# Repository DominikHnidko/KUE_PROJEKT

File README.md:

# Elektroniczny stetoskop

## 📌 Opis projektu
Projekt przedstawia **elektroniczny stetoskop** przeznaczony do precyzyjnego odsłuchu i analizy dźwięków serca.  
Umożliwia on odsłuch w czasie rzeczywistym za pomocą słuchawek lub głośnika zewnętrznego.

Głównym celem systemu jest poprawa czytelności sygnału poprzez redukcję szumów i zakłóceń.

---

## ⚙️ Najważniejsze funkcje
- Odsłuch dźwięków serca w czasie rzeczywistym
- Wyjście audio przez słuchawki lub głośnik
- Wieloetapowa filtracja sygnału
- Redukcja:
  - zakłóceń sieciowych (50/60 Hz)
  - szumów otoczenia
  - częstotliwości spoza zakresu pracy serca
- Poprawa wykrywania szmerów sercowych

Układ działa i wzmacnia sygnał z pasma pracy serca.

---

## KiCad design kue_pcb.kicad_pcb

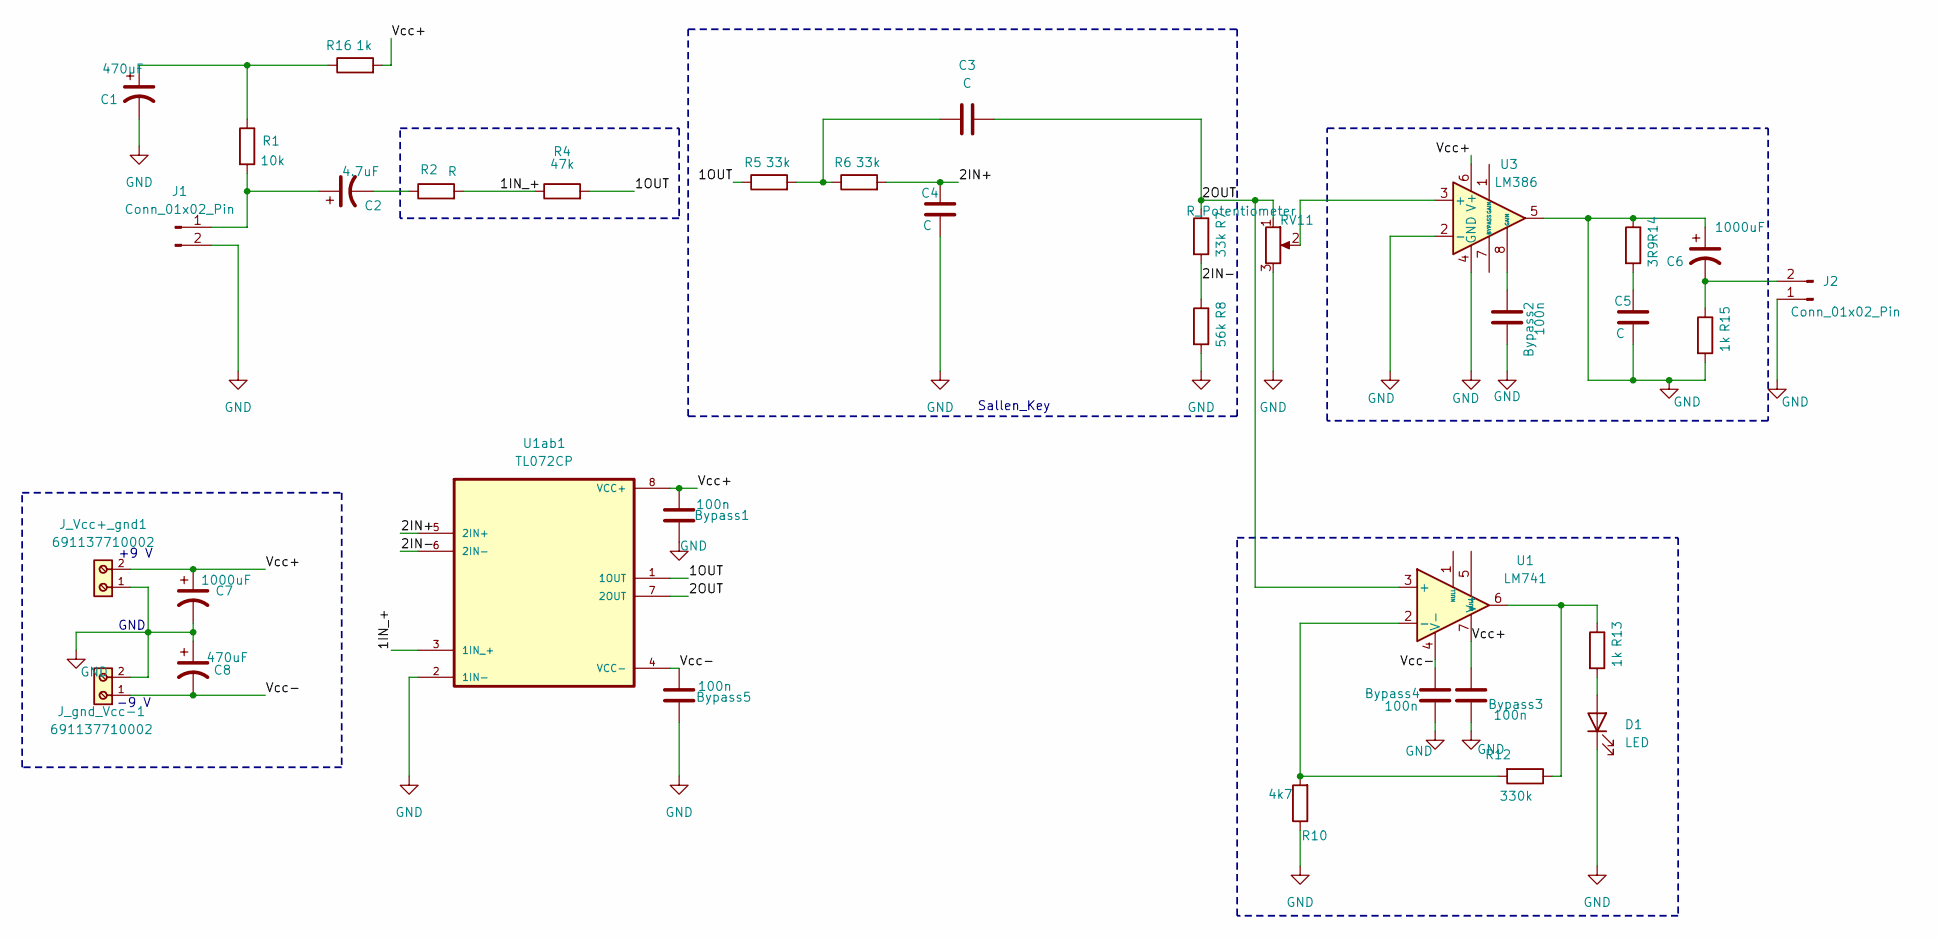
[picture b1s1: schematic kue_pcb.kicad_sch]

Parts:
Bypass1, Bypass2, Bypass3, Bypass4, Bypass5: 100n; XTAL_ZTA-2.44MG_100n_BP
C1, C8: 470uF; CAP_470uF_16V_kue
C2: 4.7uF; CAP_470uF_16V_kue
C3, C4: C; XTAL_ZTA-4.00MG_WIMA
C5: C; CAPRR254W54L508T318H736_ceramic
C6, C7: 1000uF; CP_Radial_D10.0mm_P5.00mm
D1: LED; LED_D5.0mm_Clear
J1, J2: Conn_01x02_Pin; Samtec_HPM-02-01-x-S_Straight_1x02_Pitch5.08mm
J_Vcc+_gnd1: 691137710002
J_gnd_Vcc-1: 691137710002
R1: 10k; STA_CF14_STP_kue10k_0.25w
R2: R; 2k2_kue_0.25W
R4: 47k; 47k_kue_0.25W
R5, R6: 33k; 1k_kue_0.25W
R7: 33k; 2k2_kue_0.25W
R8: 56k; 1k_kue_0.25W
R10: 4k7; 1k_kue_0.25W
R12: 330k; 1k_kue_0.25W
R13, R15, R16: 1k; 1k_kue_0.25W
R14: 3R9; 47k_kue_0.25W
RV11: R_Potentiometer; Potentiometer_Alps_RK163_Single_Horizontal
U1: LM741; DIP794W45P254L959H508Q8
U1ab1: TL072CP; DIP794W45P254L959H508Q8
U3: LM386; DIP794W45P254L959H508Q8_LM386

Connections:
/1IN_+: R2.2, R4.1, U1ab1.3 (1IN_+)
/1OUT: R4.2, R5.1, U1ab1.1 (1OUT)
/2IN+: C4.1, R6.2, U1ab1.5 (2IN+)
/2IN-: R7.2, R8.1, U1ab1.6 (2IN-)
/2OUT: C3.2, R7.1, RV11.1, U1.3 (+), U1ab1.7 (2OUT)
/Vcc+: Bypass1.1, Bypass3.1, C7.1, J_Vcc+_gnd1.2, R16.2, U1.7 (V+), U1ab1.8 (VCC+), U3.6 (V+)
/Vcc-: Bypass4.2, Bypass5.1, C8.2, J_gnd_Vcc-1.1, U1.4 (V-), U1ab1.4 (VCC-)
GND: Bypass1.2, Bypass2.1, Bypass3.2, Bypass4.1, Bypass5.2, C1.2, C4.2, C5.2, C6.1, C7.2, C8.1, D1.1 (K), J1.2, J2.1, J_Vcc+_gnd1.1, J_gnd_Vcc-1.2, R8.2, R10.1, R14.1, R15.2, RV11.3, U1ab1.2 (1IN-), U3.2 (-), U3.4 (GND), U3.5
unnamed: Bypass2.2, U3.8 (GAIN)
unnamed: C1.1, R1.1, R16.1
unnamed: C2.2, R2.1
unnamed: C3.1, R5.2, R6.1
unnamed: C5.1, R14.2
unnamed: D1.2 (A), R13.2
unnamed: C2.1, J1.1, R1.2
unnamed: C6.2, J2.2, R15.1
unnamed: R12.1, R13.1, U1.6
unnamed: R10.2, R12.2, U1.2 (-)
unnamed: RV11.2, U3.3 (+)

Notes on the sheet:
+9 V
GND
Sallen_Key
-9 V

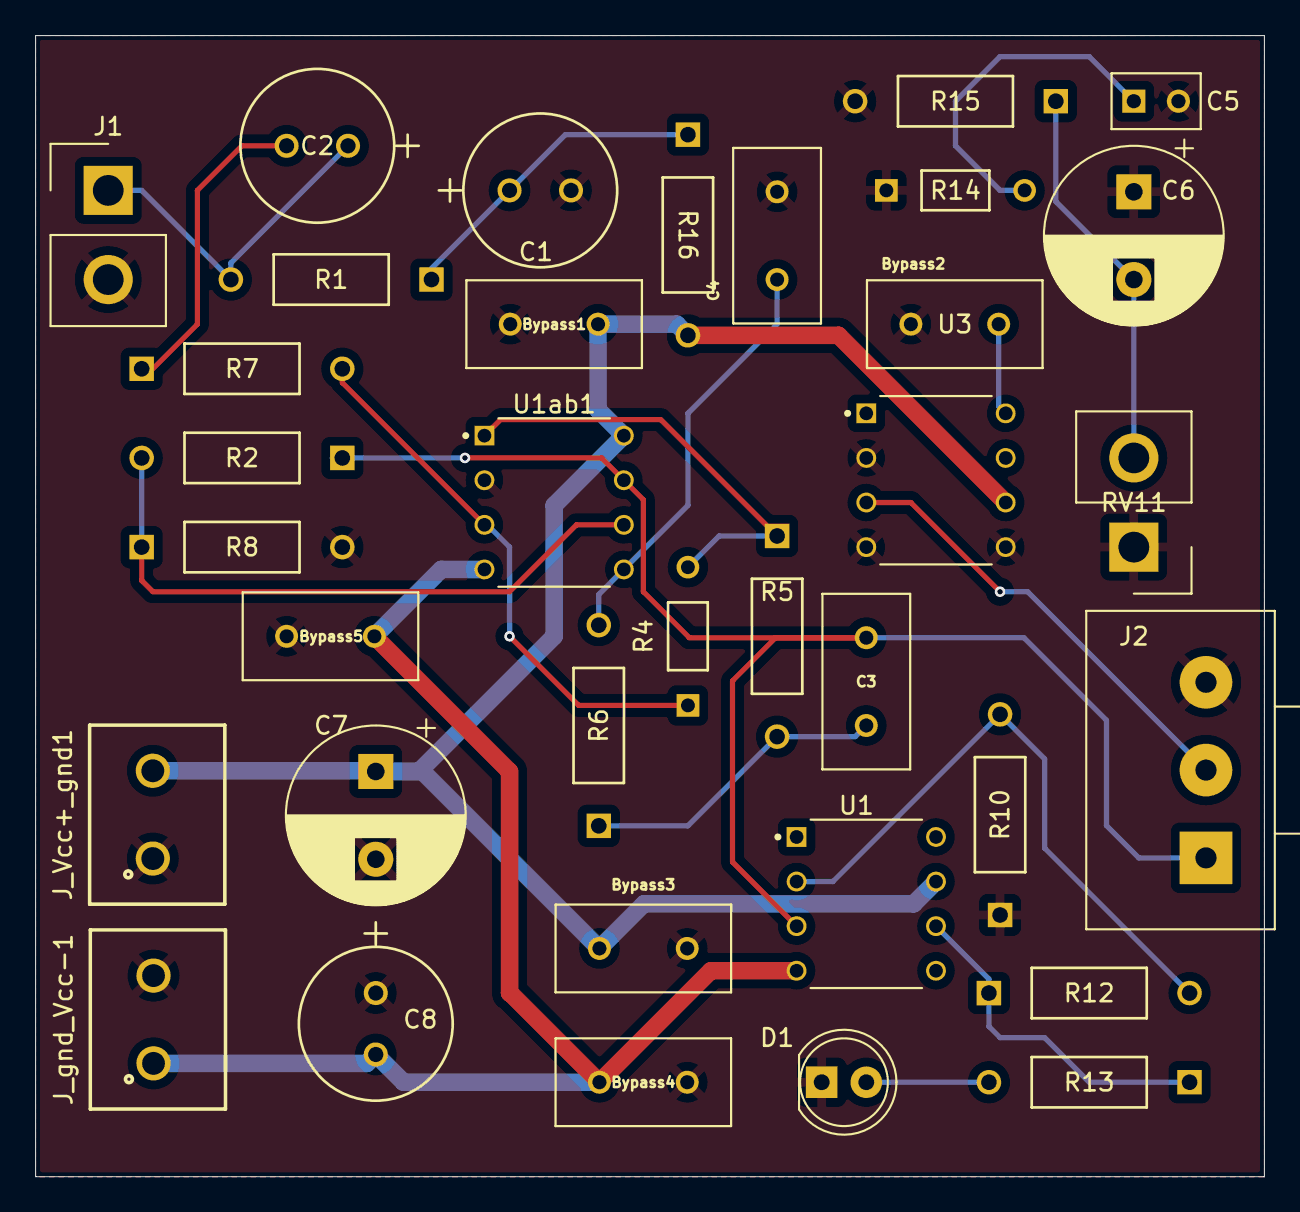
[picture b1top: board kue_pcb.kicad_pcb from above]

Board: 2 copper layers, 70.0 x 65.0 mm, 35 parts (0 on the bottom side), 19 nets.

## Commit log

2025-05-11 Add files via upload
    przed zmiana symbolu TL072
2026-04-07 Revise README with project details and features
    Updated README to provide detailed project description and features for the electronic stethoscope.
2026-04-07 Revise README by removing detailed project sections
    Removed sections on signal processing, project goals, hardware implementation, applications, and cautionary notes.
2026-04-07 Remove author section from README
    Removed author section from README.
